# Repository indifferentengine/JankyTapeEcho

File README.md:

# Indifferent Engine Janky Tape Echo

An open-source, DIY tape echo effect pedal built from a cheap cassette player and 3D printed parts.

# Demo Video

This is kinda what this thing sounds like.

# License

This device is licensed under GNU GPL v3. This means you are free to take this device and make any changes you like and then share those changes freely, **so long as you make the source for your changes publicly available**. This benefits everyone - because if you make some improvement, we can all benefit from it.

However, you **cannot distribute compiled versions.** In this context (a hardware device with software components), this effectively means you

a)  **cannot sell any physically manufactured device of any kind - either as parts or assembled.** 

b) **cannot charge money for access to any source, CAD files or software components that you choose to distribute** that are based upon this project.
  
If you **break these simple rules** we will force you to be front row at one of our floor shows, where we can **full-throat scream right in your sad little face.**

Everything is copyright (c) 2023 Indifferent Engine Ltd. Everything. OK?
Indifferent Engine and the Indifferent Engine glitch logo are trademarks of Indifferent Engine Ltd.

# What You Get

* STL files for 3D printed parts
* Gerber files for PCBs
* Source code for Arduino
* Bill of Materials
* CAD files in Step format.
* Eagle schematic files.
* Eagle board blanks (boards of correct dimensions with Jacks in correct locations).
* Build instructions (via our website)

# What You Don't Get

* Full Eagle board files
* Any support from us what-so-ever.

# Build guide

To show you how to put one of these together, there is a [build guide](https://www.indifferentengine.com/tapeechobuildguide) on our website.

# PCB

We sell PCBs for this project on our [merch store](https://www.indifferentengine.com/shop).

# How can we support you?

Indifferent Engine is a band, so go check out our music here:
[spotify](https://open.spotify.com/artist/0dltTUV2N49r1UjUTsqe3h?si=cdwmojcwTOmE14S_XvX_6A)

If you're having a crack at building an echo, maybe buy some parts from us on our [merch store](https://www.indifferentengine.com/shop).. All money goes back into the band for funding musical endeavours and more weird, open source pedal designs.

You can also follow us in the usual places:
[instagram](https://www.instagram.com/indifferentengine)
[facebook](https://www.facebook.com/indifferentengine)
[tiktok](https://www.tiktok.com/@indifferentengine)
[youtube](https://www.youtube.com/@indifferentengine)

And **buy a T-Shirt while you're at it**, you bunch of scallywags.

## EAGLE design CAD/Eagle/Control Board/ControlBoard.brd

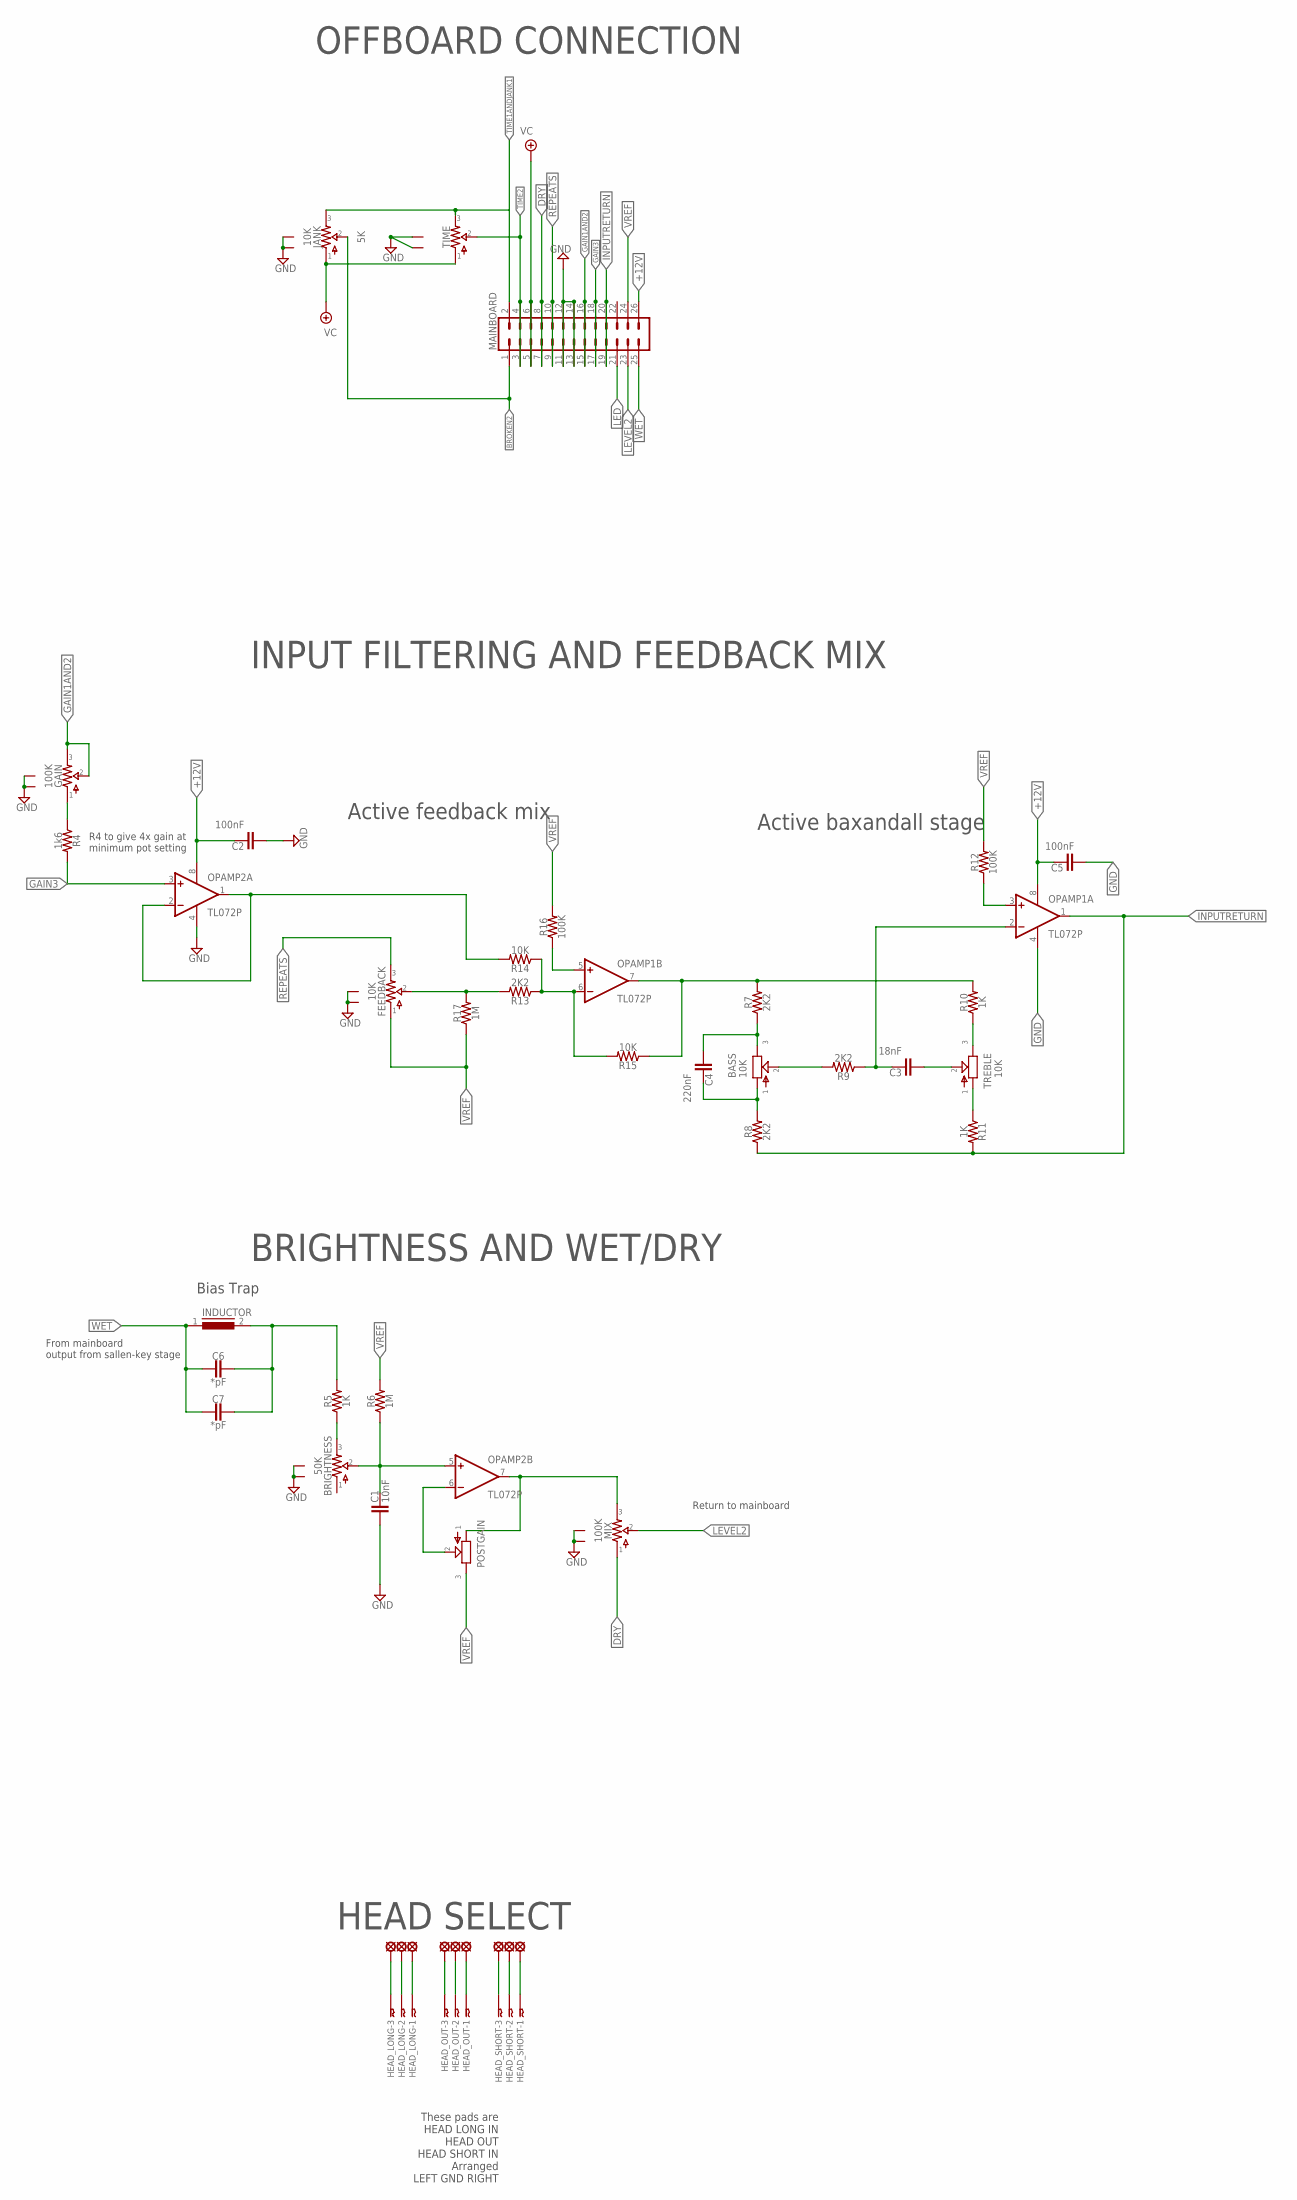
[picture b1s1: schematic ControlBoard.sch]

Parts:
BASS: 10K; B375P
BRIGHTNESS: 50K; 9MM_METAL_SHAFT
C1: 10nF; .33UF+
C2, C5: 100nF; 5MM
C3: 18nF; .33UF+
C4: 220nF; .33UF+
C6, C7: *pF; .33UF+
FEEDBACK: 10K; 9MM_METAL_SHAFT
GAIN: 100K; 9MM_METAL_SHAFT
HEAD_LONG: 03-JST-B3B-XH-A; B3B-XH
HEAD_OUT: 03-JST-B3B-XH-A; B3B-XH
HEAD_SHORT: 03-JST-B3B-XH-A; B3B-XH
HIN_1, HIN_2, HIN_3, HIN_4, HIN_5, HIN_6: SE14
HOUT_1, HOUT_2, HOUT_3: SE14
INDUCTOR: 82114R
JANK: 10K; 9MM_METAL_SHAFT
MAINBOARD: CONN_13X22X13; 2X13
MIX: 100K; 9MM_METAL_SHAFT
OPAMP1, OPAMP2: TL072P; DIL08
POSTGAIN: POT-EU375; B375P
R4: 1k6; 7.5MM.2
R5, R10, R11: 1K; 7.5MM.2
R6, R17: 1M; 7.5MM.2
R7, R8, R9, R13: 2K2; 7.5MM.2
R12, R16: 100K; 7.5MM.2
R14, R15: 10K; 7.5MM.2
TIME: 5K; 9MM_METAL_SHAFT
TREBLE: 10K; B375P

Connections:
+12V: C2.1, C5.1, MAINBOARD.26, OPAMP1.8 (V+), OPAMP2.8 (V+)
BIAS: C6.1, C7.1, INDUCTOR.2, R5.2
BRIGHTNESS2: OPAMP2.1 (OUT), OPAMP2.2 (-IN), R14.2
BROKEN2: JANK.P$2 (2), MAINBOARD.1
DRY: MAINBOARD.7, MAINBOARD.8, MIX.P$1 (1)
GAIN1AND2: GAIN.P$2 (2), GAIN.P$3 (3), MAINBOARD.15, MAINBOARD.16
GAIN3: MAINBOARD.17, MAINBOARD.18, OPAMP2.3 (+IN), R4.2
GND: BRIGHTNESS.P$4 (CHAS$1), BRIGHTNESS.P$5 (CHAS$2), C1.2, C2.2, C5.2, FEEDBACK.P$4 (CHAS$1), FEEDBACK.P$5 (CHAS$2), GAIN.P$4 (CHAS$1), GAIN.P$5 (CHAS$2), JANK.P$4 (CHAS$1), JANK.P$5 (CHAS$2), MAINBOARD.11, MAINBOARD.12, MAINBOARD.13, MAINBOARD.14, MIX.P$4 (CHAS$1), MIX.P$5 (CHAS$2), OPAMP1.4 (V-), OPAMP2.4 (V-), TIME.P$4 (CHAS$1), TIME.P$5 (CHAS$2)
INPUTRETURN: MAINBOARD.19, MAINBOARD.20, OPAMP1.1 (OUT), R8.1, R11.2
LED: MAINBOARD.21
LEVEL2: MAINBOARD.23, MIX.P$2 (2)
unnamed: BRIGHTNESS.P$2 (2), C1.1, OPAMP2.5 (+IN), R6.1
unnamed: HEAD_LONG.P$3, HIN_4.MP
unnamed: BASS.2, R9.2
unnamed: R10.1, TREBLE.3
unnamed: C3.2, TREBLE.2
unnamed: HEAD_LONG.P$2, HIN_5.MP
unnamed: HEAD_LONG.P$1, HIN_6.MP
unnamed: HEAD_OUT.P$3, HOUT_1.MP
unnamed: BRIGHTNESS.P$3 (3), R5.1
unnamed: HEAD_OUT.P$2, HOUT_2.MP
unnamed: HEAD_OUT.P$1, HOUT_3.MP
unnamed: OPAMP2.6 (-IN), POSTGAIN.2
unnamed: MIX.P$3 (3), OPAMP2.7 (OUT), POSTGAIN.1
unnamed: HEAD_SHORT.P$3, HIN_1.MP
unnamed: BASS.3, C4.2, R7.1
unnamed: BASS.1, C4.1, R8.2
unnamed: R11.1, TREBLE.1
unnamed: FEEDBACK.P$2 (2), R13.2, R17.2
unnamed: C3.1, OPAMP1.2 (-IN), R9.1
unnamed: OPAMP1.3 (+IN), R12.1
unnamed: OPAMP1.6 (-IN), R13.1, R14.1, R15.2
unnamed: OPAMP1.5 (+IN), R16.1
unnamed: HEAD_SHORT.P$2, HIN_2.MP
unnamed: HEAD_SHORT.P$1, HIN_3.MP
unnamed: GAIN.P$1 (1), R4.1
REPEATS: FEEDBACK.P$3 (3), MAINBOARD.9, MAINBOARD.10
TIME1ANDJANK1: JANK.P$3 (3), MAINBOARD.2, TIME.P$3 (3)
TIME2: MAINBOARD.3, MAINBOARD.4, TIME.P$2 (2)
TOBAXANDALL: OPAMP1.7 (OUT), R7.2, R10.2, R15.1
VC: JANK.P$1 (1), MAINBOARD.5, MAINBOARD.6, TIME.P$1 (1)
VREF: FEEDBACK.P$1 (1), MAINBOARD.24, POSTGAIN.3, R6.2, R12.2, R16.2, R17.1
WET: C6.2, C7.2, INDUCTOR.1, MAINBOARD.25

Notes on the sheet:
OFFBOARD CONNECTION
These pads are HEAD LONG IN HEAD OUT HEAD SHORT IN Arranged LEFT GND RIGHT
INPUT FILTERING AND FEEDBACK MIX
BRIGHTNESS AND WET/DRY
HEAD SELECT
R4 to give 4x gain at minimum pot setting
Active baxandall stage
Active feedback mix
Return to mainboard
From mainboard output from sallen-key stage
Bias Trap

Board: 2 copper layers, 46 parts (0 on the bottom side), 42 nets, no tracks yet.

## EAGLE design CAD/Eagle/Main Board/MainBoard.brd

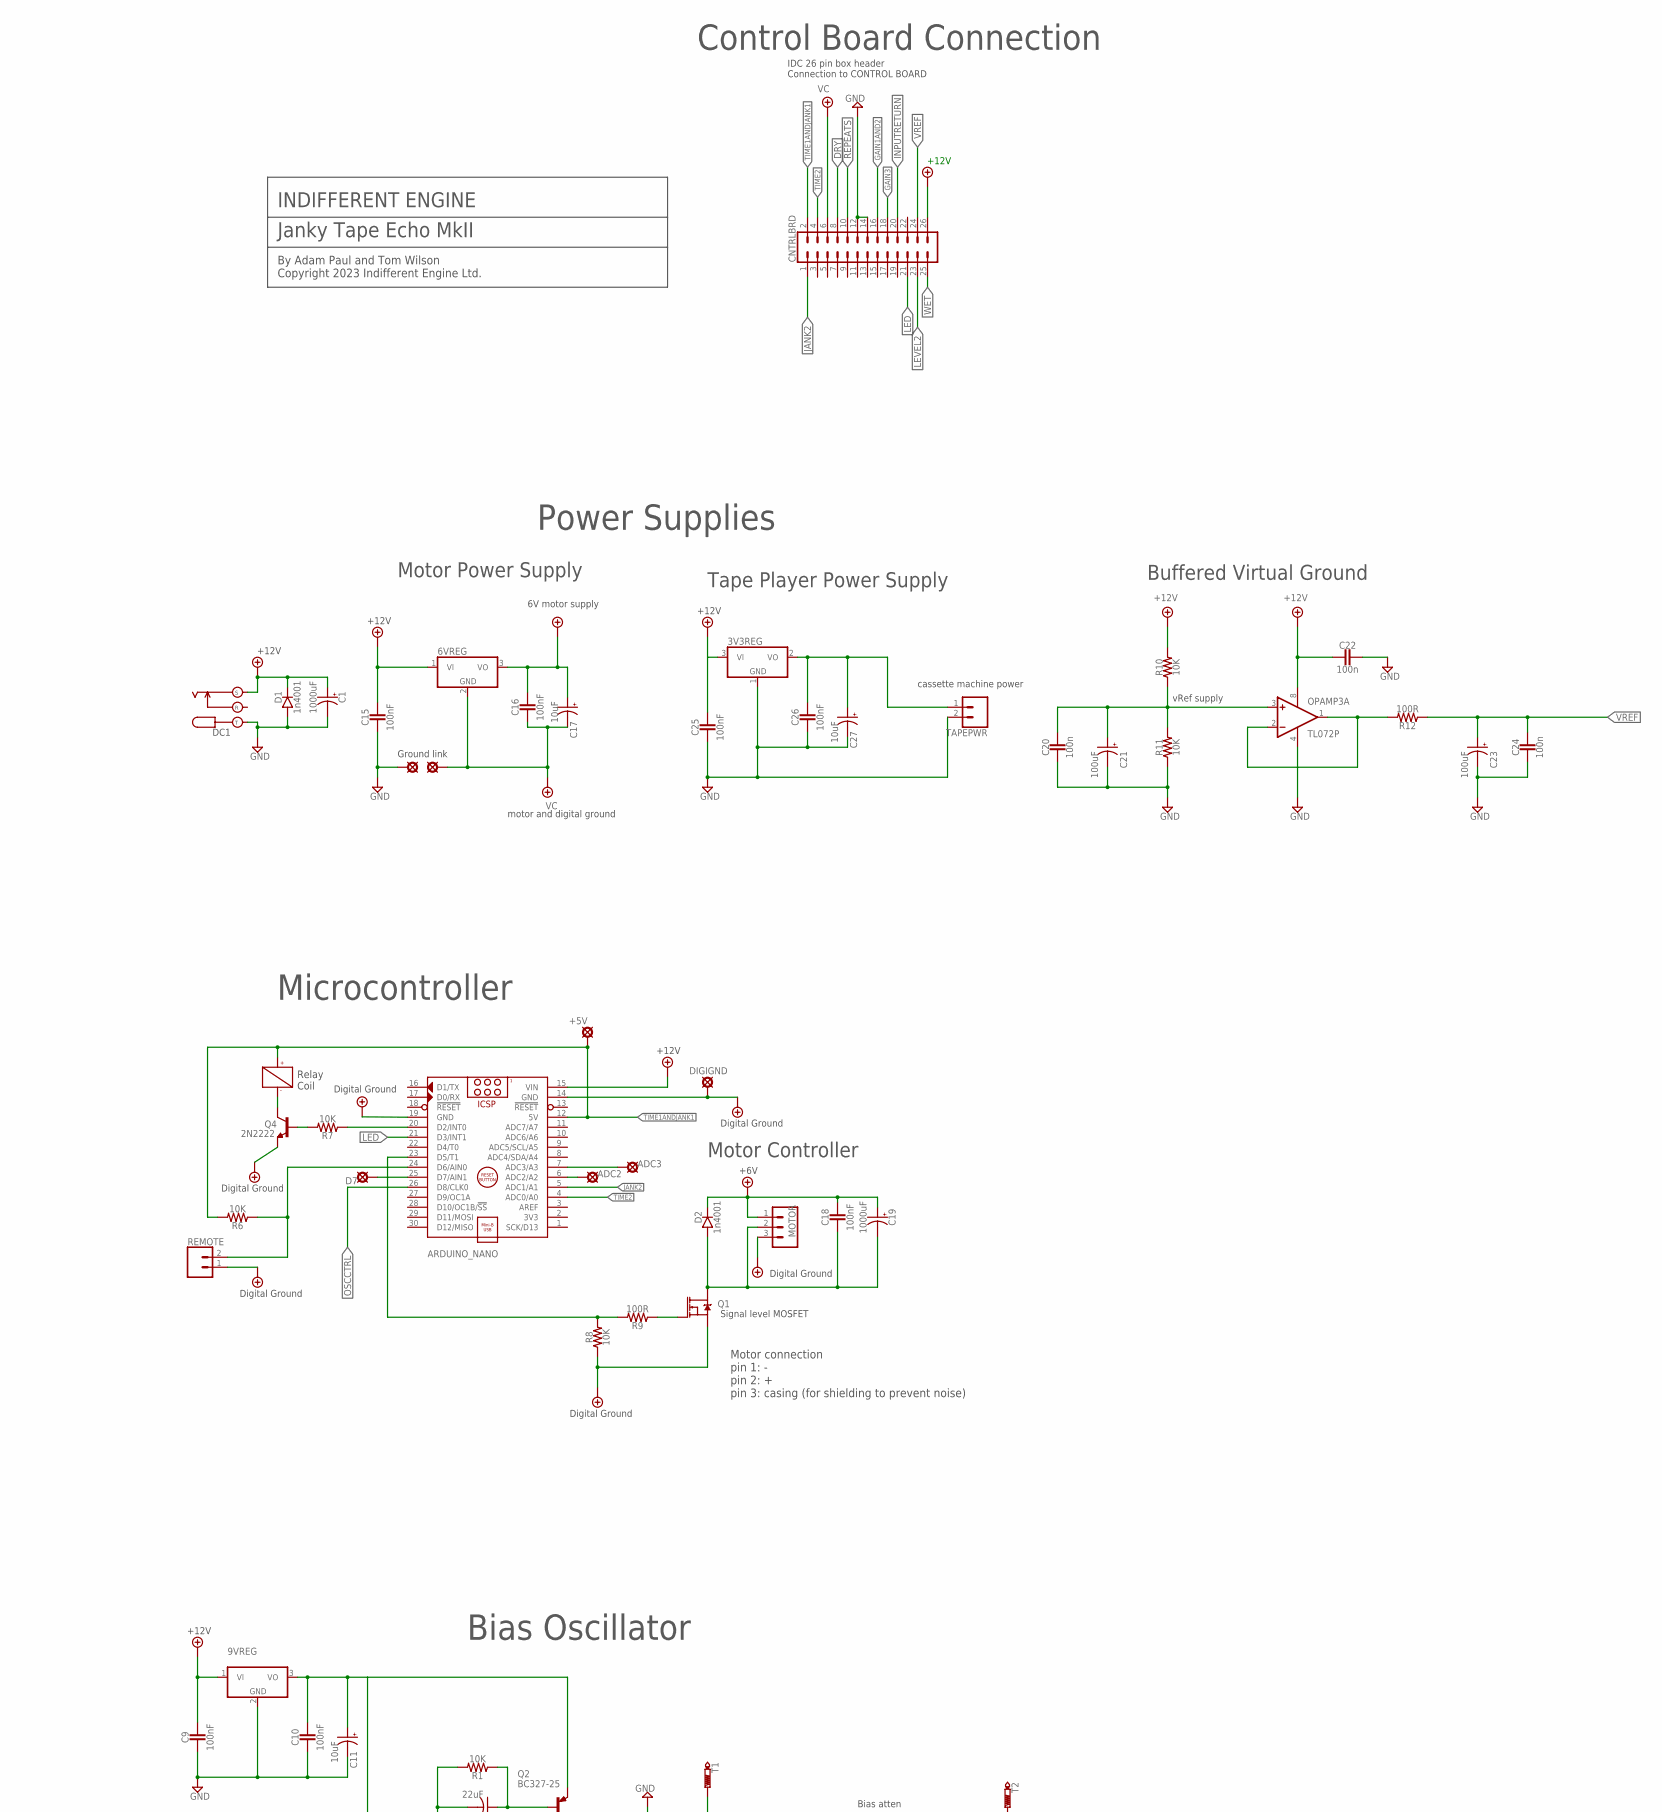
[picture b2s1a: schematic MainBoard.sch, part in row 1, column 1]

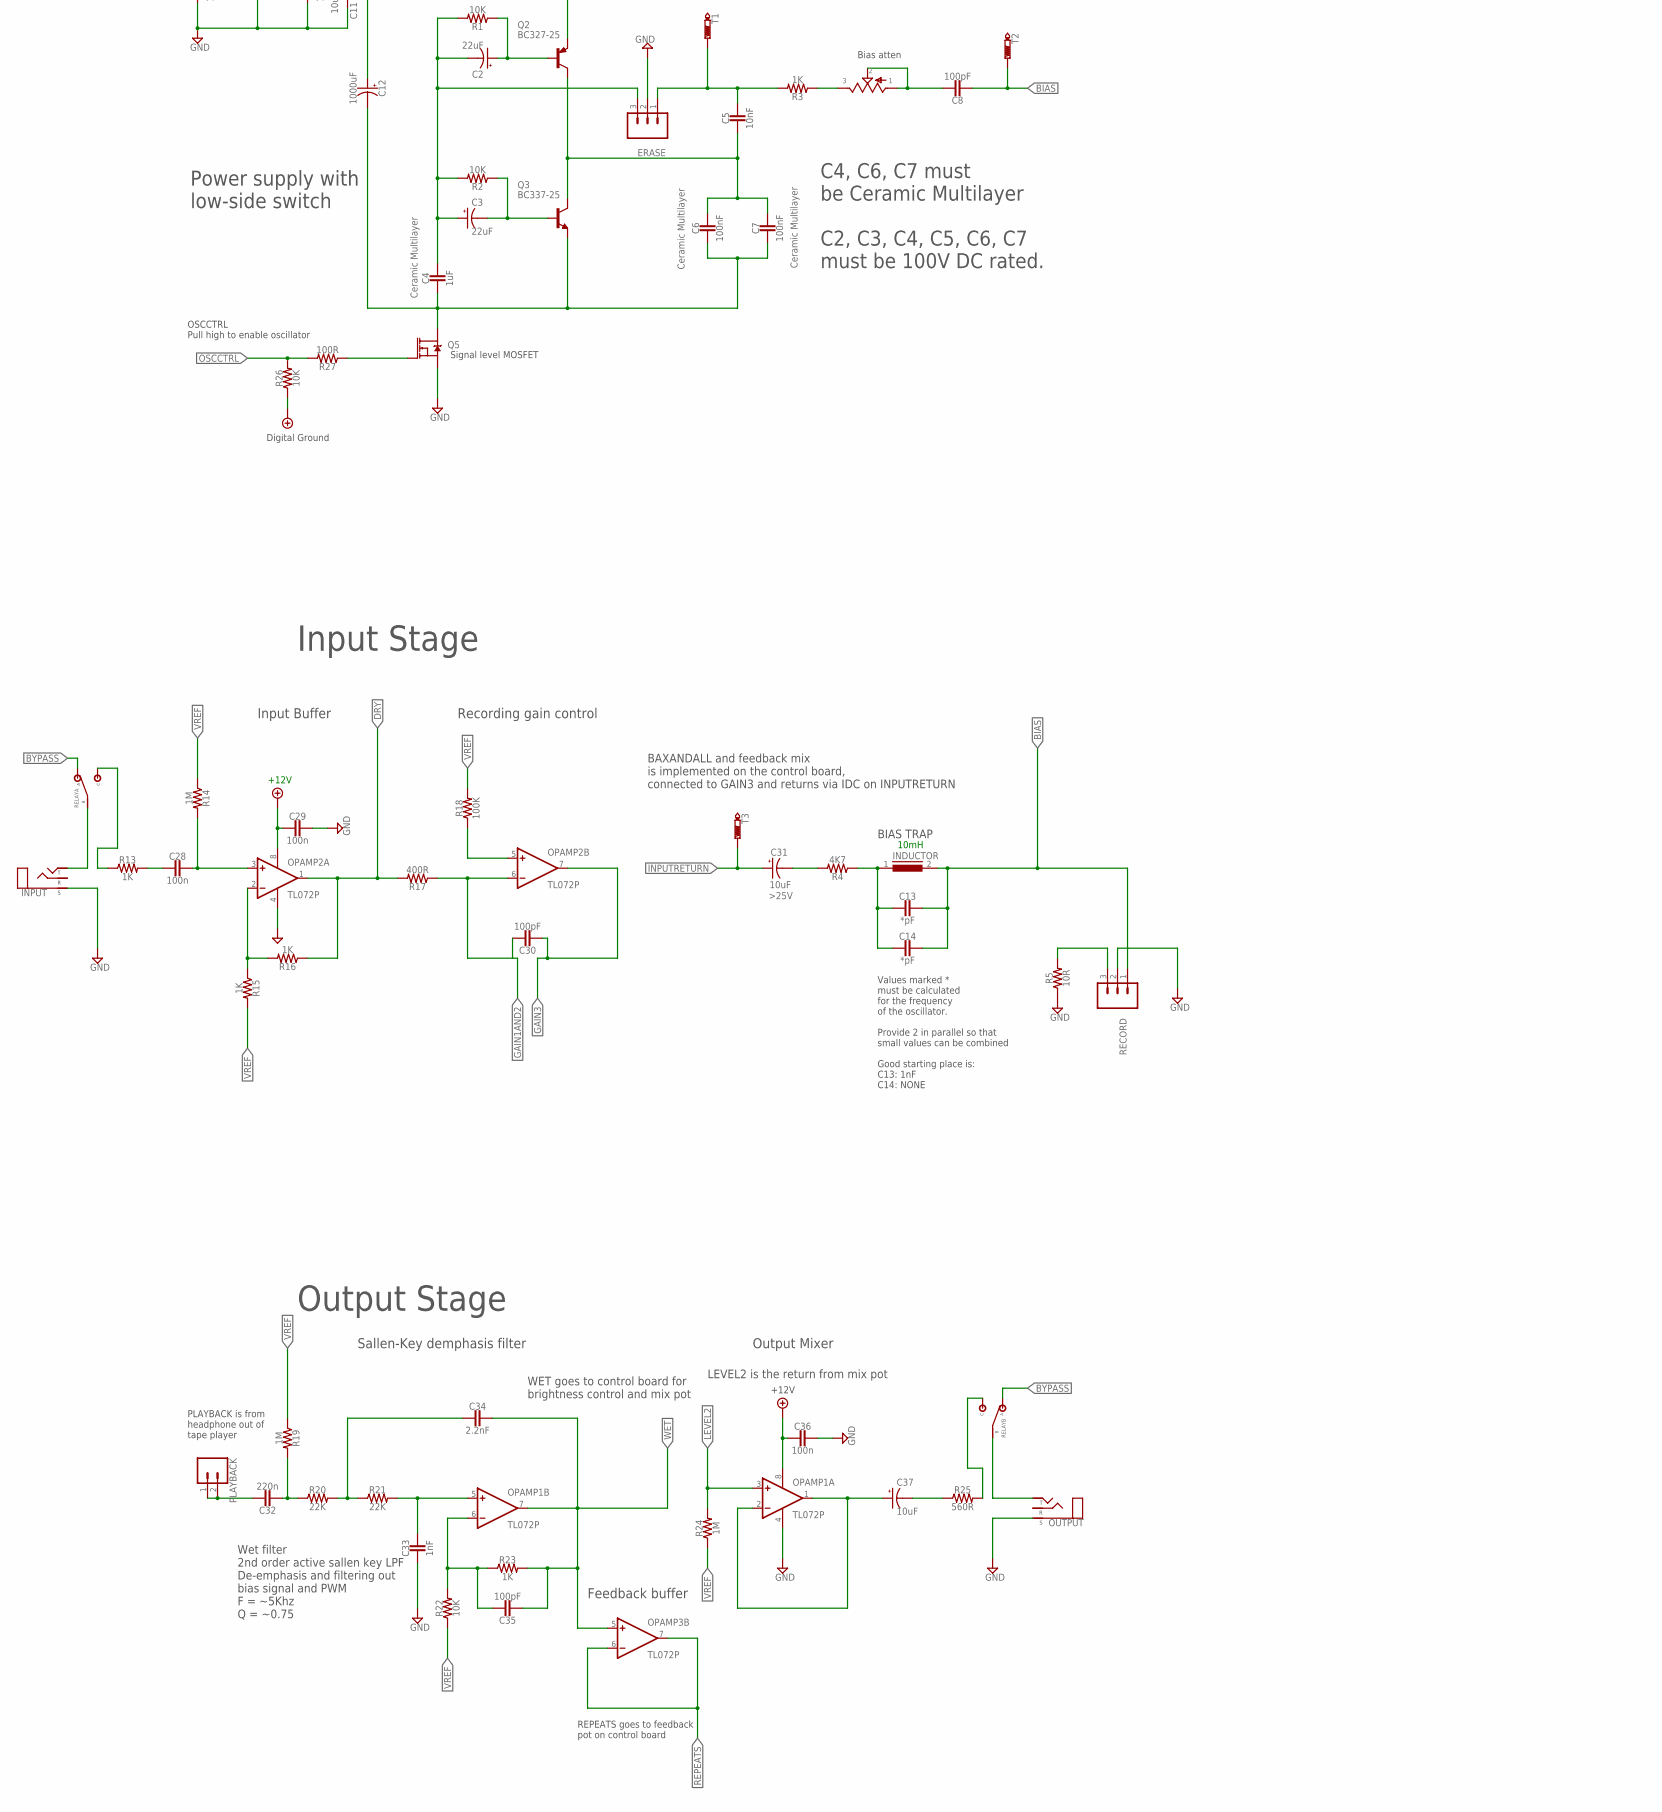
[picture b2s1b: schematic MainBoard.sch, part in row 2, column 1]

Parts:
3V3REG: 78TO220H_2_SMALL; TO220H_SMALL
6VREG, 9VREG: 78TO220H_SMALL; TO220H_SMALL
+5V: PADL; LONG
ADC2, ADC3: PADL; LONG
ANALOG_GND: PADL; LONG
ARDUINO_NANO: ARDUINO_NANO
BIASLEVEL: POTTRIM3/8; B375P
C1, C12, C19: 1000uF; 080_5MM
C2, C3: 22uF; 050_2.5MM.1
C4: 1uF; 5MM
C5: 10nF; 5MM
C6, C7, C9, C10, C15, C16, C25, C26: 100nF; 5MM
C8, C30, C35: 100pF; .33UF+
C11, C17, C27, C37: 10uF; 050_2.5MM.1
C13, C14: *pF; .33UF+
C18: 100nF; .33UF+
C20, C22, C24, C29, C36: 100n; 5MM
C21, C23: 100uF; 050_2.5MM.1
C28: 100n; .33UF+
C31: 10uF; 050_2.5MM.1; VOLTAGE >25V
C32: 220n; .33UF+
C33: 1nF; .33UF+
C34: 2.2nF; .33UF+
CNTRLBRD: CONN_13X22X13; 2X13
D1, D2: 1n4001; DO41-3
D7: PADL; LONG
DC1: DC_KOBICONN
DIGIGND: PADL; LONG
DIGI_GROUND: PADL; LONG
ERASE: 455-1750-1-ND; 1X03
INDUCTOR: 82114R
INPUT: STEREO; STEREO_PCB
MOTOR: 455-1750-1-ND; 1X03
OPAMP1, OPAMP2, OPAMP3: TL072P; DIL08
OUTPUT: STEREO; STEREO_PCB
PLAYBACK: CONN_02; 1X02
Q1, Q5: 60V/32A/35mΩ; TO220V
Q2: BC327-25; TO92-EBC
Q3: BC337-25TO92; TO92-EBC
Q4: 2N2222; TO92-
R1, R2, R6, R7, R8, R10, R11, R22, R26: 10K; 7.5MM.2
R3, R13, R15, R16, R23: 1K; 7.5MM.2
R4: 4K7; 7.5MM.2
R5: 10R; 7.5MM.2
R9, R12, R27: 100R; 7.5MM.2
R14, R19, R24: 1M; 7.5MM.2
R17: 400R; 7.5MM.2
R18: 100K; 7.5MM.2
R20, R21: 22K; 7.5MM.2
R25: 560R; 7.5MM.2
RECORD: 455-1750-1-ND; 1X03
RELAY: IM02TSIM02TS; 8-PIN
REMOTE: CONN_02; 1X02
T1, T2, T3: PTR1B2,54; B2,54
TAPEPWR: CONN_02; 1X02

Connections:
+12V: 3V3REG.3 (VI), 6VREG.1 (VI), 9VREG.1 (VI), ARDUINO_NANO.15 (VIN), C1.+, C9.1, C15.1, C22.2, C25.1, C29.2, C36.2, CNTRLBRD.26, D1.C, DC1.S, OPAMP1.8 (V+), OPAMP2.8 (V+), OPAMP3.8 (V+), R10.2
BIAS: C8.2, C13.1, C14.1, INDUCTOR.2, RECORD.1, T2.TP
BYPASS: RELAY.3 (A), RELAY.10 (A)
DRY: CNTRLBRD.8, OPAMP2.1 (OUT), R16.1, R17.2
GAIN1AND2: C30.1, CNTRLBRD.16, OPAMP2.6 (-IN), R17.1
GAIN3: C30.2, CNTRLBRD.18, OPAMP2.7 (OUT)
GND: 3V3REG.1 (GND), 9VREG.2 (GND), ANALOG_GND.1, C1.-, C9.2, C10.2, C11.-, C15.2, C20.2, C21.-, C22.1, C23.-, C24.2, C25.2, C26.2, C27.-, C29.1, C33.2, C36.1, CNTRLBRD.12, CNTRLBRD.14, D1.A, DC1.T, ERASE.2, INPUT.P$1 (S), OPAMP1.4 (V-), OPAMP2.4 (V-), OPAMP3.4 (V-), OUTPUT.P$1 (S), Q5.3 (S), R5.1, R11.1, RECORD.2, TAPEPWR.2
INPUTRETURN: C31.+, CNTRLBRD.20, T3.TP
JANK2: ARDUINO_NANO.5 (ADC1/A1), CNTRLBRD.1
LED: ARDUINO_NANO.21 (D3/INT1), CNTRLBRD.21
LEVEL2: CNTRLBRD.23, OPAMP1.3 (+IN), R24.2
unnamed: INPUT.P$3 (T), RELAY.4 (B)
unnamed: ARDUINO_NANO.23 (D5/T1), R8.2, R9.2
unnamed: C18.2, C19.-, D2.A, MOTOR.2, Q1.2 (D)
unnamed: Q1.1 (G), R9.1
unnamed: C28.2, R13.2
unnamed: OPAMP2.5 (+IN), R18.1
unnamed: OPAMP2.2 (-IN), R15.1, R16.2
unnamed: C13.2, C14.2, INDUCTOR.1, R4.1
unnamed: Q5.1 (G), R27.1
unnamed: R5.2, RECORD.3
unnamed: R13.1, RELAY.5 (C)
unnamed: C33.1, OPAMP1.5 (+IN), R21.2
unnamed: C32.2, R19.2, R20.1
unnamed: C35.1, OPAMP1.6 (-IN), R22.2, R23.1
unnamed: C20.1, C21.+, OPAMP3.3 (+IN), R10.1, R11.2
unnamed: C34.2, R20.2, R21.1
unnamed: C28.1, OPAMP2.3 (+IN), R14.2
unnamed: C37.+, OPAMP1.1 (OUT), OPAMP1.2 (-IN)
unnamed: C37.-, R25.1
unnamed: R25.2, RELAY.8 (C)
unnamed: C2.+, Q2.B, R1.1
unnamed: C3.-, Q3.B, R2.1
unnamed: C2.-, C3.+, C4.1, ERASE.3, R1.2, R2.2
unnamed: C5.2, C6.1, C7.1, Q2.C, Q3.C
unnamed: C5.1, ERASE.1, R3.2, T1.TP
unnamed: BIASLEVEL.3, R3.1
unnamed: OUTPUT.P$3 (T), RELAY.9 (B)
unnamed: Q4.2 (B), R7.2
unnamed: BIASLEVEL.1, BIASLEVEL.2, C8.1
unnamed: C31.-, R4.2
unnamed: ARDUINO_NANO.20 (D2/INT0), R7.1
unnamed: Q4.1 (C), RELAY.1 (-)
unnamed: ARDUINO_NANO.24 (D6/AIN0), R6.1, REMOTE.2
unnamed: OPAMP3.1 (OUT), OPAMP3.2 (-IN), R12.2
unnamed: 9VREG.3 (VO), C10.1, C11.+, C12.+, Q2.E
unnamed: 3V3REG.2 (VO), C26.1, C27.+, TAPEPWR.1
unnamed: C4.2, C6.2, C7.2, C12.-, Q3.E, Q5.2 (D)
unnamed: ADC2.1, ARDUINO_NANO.6 (ADC2/A2)
unnamed: ADC3.1, ARDUINO_NANO.7 (ADC3/A3)
unnamed: ARDUINO_NANO.25 (D7/AIN1), D7.1
OSCCTRL: ARDUINO_NANO.26 (D8/CLK0), R26.2, R27.2
PLAYBACK: C32.1, PLAYBACK.1, PLAYBACK.2
REPEATS: CNTRLBRD.10, OPAMP3.6 (-IN), OPAMP3.7 (OUT)
TIME1ANDJANK1: +5V.1, ARDUINO_NANO.12 (5V), CNTRLBRD.2, R6.2, RELAY.12 (+)
TIME2: ARDUINO_NANO.4 (ADC0/A0), CNTRLBRD.4
VC: 6VREG.2 (GND), ARDUINO_NANO.14 (GND), ARDUINO_NANO.19 (GND), C16.2, C17.-, CNTRLBRD.6, DIGIGND.1, DIGI_GROUND.1, MOTOR.3, Q1.3 (S), Q4.3 (E), R8.1, R26.1, REMOTE.1
VD: 6VREG.3 (VO), C16.1, C17.+, C18.1, C19.+, D2.C, MOTOR.1
VREF: C23.+, C24.1, CNTRLBRD.24, R12.1, R14.1, R15.2, R18.2, R19.1, R22.1, R24.1
WET: C34.1, C35.2, CNTRLBRD.25, OPAMP1.7 (OUT), OPAMP3.5 (+IN), R23.2

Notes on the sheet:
6V motor supply
Motor Power Supply
Motor Controller
Input Buffer
vRef supply
BIAS TRAP
Wet filter 2nd order active sallen key LPF De-emphasis and filtering out bias signal and PWM F = ~5Khz Q = ~0.75
Output Mixer
BC337-25
Ceramic Multilayer
IDC 26 pin box header Connection to CONTROL BOARD
10mH
Bias atten
+12V
Relay Coil
Digital Ground
+6V
Signal level MOSFET
Control Board Connection
INDIFFERENT ENGINE
Janky Tape Echo MkII
By Adam Paul and Tom Wilson Copyright 2023 Indifferent Engine Ltd.
motor and digital ground
cassette machine power
Values marked * must be calculated for the frequency of the oscillator. Provide 2 in parallel so that small values can be combined Good starting place is: C13: 1nF C14: NONE
REPEATS goes to feedback pot on control board
Feedback buffer
PLAYBACK is from headphone out of tape player
Recording gain control
BAXANDALL and feedback mix is implemented on the control board, connected to GAIN3 and returns via IDC on INPUTRETURN
Power Supplies
Buffered Virtual Ground
Microcontroller
Bias Oscillator
Input Stage
Output Stage
Motor connection pin 1: - pin 2: + pin 3: casing (for shielding to prevent noise)
OSCCTRL Pull high to enable oscillator
Tape Player Power Supply
Power supply with low-side switch

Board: 2 copper layers, 101 parts (0 on the bottom side), 60 nets, no tracks yet.

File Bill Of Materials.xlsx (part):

This page contains the electronic parts in order of usage in the build instruct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
The Jacks
Part | Value | Description | Notes
INPUT | Audio Jack | PCB mount 3/4" audio jack
OUTPUT | Audio Jack | PCB mount 3/4" audio jack
DC1 | DC Jack | Boss-style 2.1mm DC Jack
The Ground Link
GND LINK | 0R | Zero Ohm Link | This is just a 0 Ohm link between the digital ground and analog ground. This is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
The JST XH Headers
ERASE | 2-way JST XH Header | 2-way JST XH Male Terminal. 2.54mm lead pitch.
PLAYBACK | 2-way JST XH Header | 2-way JST XH Male Terminal. 2.54mm lead pitch.
RECORD | 2-way JST XH Header | 2-way JST XH Male Terminal. 2.54mm lead pitch.
REMOTE | 2-way JST XH Header | 2-way JST XH Male Terminal. 2.54mm lead pitch.
TAPEPWR | 2-way JST XH Header | 2-way JST XH Male Terminal. 2.54mm lead pitch.
MOTOR | 3-way JST XH Header | 3-way JST XH Male Terminal. 2.54mm lead pitch. | We use a 3 way header because we use a spare pin to ground the motor casing. Th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
The IDC Box Header
CNTRLBRD | IDC Box Header | 26-way IDC box header for connection to control board | Must be a 26-way, 2 row IDC box header.
12V Main Supply
D1 | 1n4001 | Polarity protection diode
C1 | 1000uF | Electrolytic capacitor, 16V, 8mm diameter
9V Bias Oscillator Supply
R26 | 10K | 1/4W Metal Film Resistor, 7.5mm diameter
R27 | 100R | 1/4W Metal Film Resistor, 7.5mm diameter
C9 | 100nF | Ceramic capacitor, 16V, 5mm diameter
C10 | 100nF | Ceramic capacitor, 16V, 5mm diameter
C11 | 10uF | Electrolytic capacitor, 16V, 5mm diameter
C12 | 1000uF | Electrolytic capacitor, 16V, 8mm diameter
9VREG | 7809.0 | Positive VOLTAGE REGULATOR, 9V Output | Ensure correct pinout: INPUT, GND, OUTPUT
Q5 | RFP12N10L | N-channel, logic level MOSFET | For oscillator disable control
6V Motor Supply
6VREG | 7806.0 | Positive VOLTAGE REGULATOR, 6V Output | Ensure correct pinout: INPUT, GND, OUTPUT
C15 | 100nF | Ceramic capacitor, 16V, 5mm diameter
C16 | 100nF | Ceramic capacitor, 16V, 5mm diameter
C17 | 10uF | Electrolytic capacitor, 16V, 5mm diameter
3V3 Tape Player Supply
3V3REG | LD1086V33 | Positive VOLTAGE REGULATOR, 3.3V Output | Ensure correct pinout: GND, OUTPUT, INPUT This is different to the other 2 regu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
C25 | 100nF | Ceramic capacitor, 16V, 5mm diameter
C26 | 100nF | Ceramic capacitor, 16V, 5mm diameter
C27 | 10uF | Electrolytic capacitor, 16V, 5mm diameter
Buffered Virtual Ground
R10 | 10K | 1/4W Metal Film Resistor, 7.5mm diameter
R11 | 10K | 1/4W Metal Film Resistor, 7.5mm diameter
R12 | 100R | 1/4W Metal Film Resistor, 7.5mm diameter
OPAMP3 | TL072 | TL072 Dual Op Amp (or equivalent)
C20 | 100n | Ceramic capacitor, 16V, 5mm diameter
C21 | 100uF | Electrolytic capacitor, 16V, 5mm diameter
C22 | 100n | Ceramic capacitor, 16V, 5mm diameter
C23 | 100uF | Electrolytic capacitor, 16V, 5mm diameter
C24 | 100n | Ceramic capacitor, 16V, 5mm diameter
Arduino Nano
ARDUINO_NANO | Arduino Nano | Arduino Nano V3.0 Module
True Bypass Switching
R6 | 10K | 1/4W Metal Film Resistor, 7.5mm diameter
R7 | 10K | 1/4W Metal Film Resistor, 7.5mm diameter
Q4 | 2N2222 | NPN Transistor | For relay bypass switching
RELAY | 5-1462039-9 | Non-Latching, DPDT Signal Relay, 5V | https://uk.farnell.com/te-connectivity/im03pns/relay-signal-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
The Motor Controller
R8 | 10K | 1/4W Metal Film Resistor, 7.5mm diameter
R9 | 100R | 1/4W Metal Film Resistor, 7.5mm diameter
D2 | 1n4001 | Back propagation protection diode
Q1 | RFP12N10L | N-channel, logic level MOSFET | High current MOSFET for motor control. Must be logic level to interface with Ar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
C18 | 100nF | Ceramic capacitor, 16V, 5mm diameter
C19 | 1000uF | Electrolytic capacitor, 16V, 8mm diameter
Mainboard Input Stage
R4 | 4K7 | 1/4W Metal Film Resistor, 7.5mm diameter
R5 | 0R | 1/4W Metal Film Resistor, 7.5mm diameter | This is included as a way to adjust coil resistance for tuning purposes. If in 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
R13 | 1K | 1/4W Metal Film Resistor, 7.5mm diameter
R14 | 1M | 1/4W Metal Film Resistor, 7.5mm diameter
R15 | 1K | 1/4W Metal Film Resistor, 7.5mm diameter
R16 | 1K | 1/4W Metal Film Resistor, 7.5mm diameter
R17 | 400R | 1/4W Metal Film Resistor, 7.5mm diameter
R18 | 100K | 1/4W Metal Film Resistor, 7.5mm diameter
OPAMP2 | TL072 | TL072 Dual Op Amp (or equivalent)
C13 | *pF | Film capacitor, 100V, 5mm diameter | For tuning bias trap notch filter. A good starting place is C13 as 1nF and C14 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
C14 | *pF | Film capacitor, 100V, 5mm diameter | Optional. Extra capacitor space for combining values with C13 (to make non-stan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
C28 | 100n | Film capacitor, 16V, 5mm diameter
C29 | 100n | Ceramic capacitor, 16V, 5mm diameter
C30 | 100pF | Film capacitor, 16V, 5mm diameter
C31 | 10uF | Electrolytic capacitor, 100V, 5mm diameter | Must be 100V rated
INDUCTOR | 10mH | Radial Inductor | For bias trap. If different value used, capacitors C13 and C14 in the tank circ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
Mainboard Output Stage
R19 | 1M | 1/4W Metal Film Resistor, 7.5mm diameter
R20 | 22K | 1/4W Metal Film Resistor, 7.5mm diameter
R21 | 22K | 1/4W Metal Film Resistor, 7.5mm diameter
R22 | 10K | 1/4W Metal Film Resistor, 7.5mm diameter
R23 | 1K | 1/4W Metal Film Resistor, 7.5mm diameter
R24 | 1M | 1/4W Metal Film Resistor, 7.5mm diameter
R25 | 560R | 1/4W Metal Film Resistor, 7.5mm diameter
OPAMP1 | TL072 | TL072 Dual Op Amp (or equivalent)
C32 | 220n | Film capacitor, 16V, 5mm diameter
C33 | 1nF | Film capacitor, 16V, 5mm diameter
C34 | 2.2nF | Film capacitor, 16V, 5mm diameter
C35 | 100pF | Film capacitor, 16V, 5mm diameter
C36 | 100n | Ceramic capacitor, 16V, 5mm diameter
C37 | 10uF | Electrolytic capacitor, 16V, 5mm diameter
Control Board IDC Header
MAINBOARD | IDC Box Header | 26-way IDC box header for connection to control board | Must be a 26-way, 2 row IDC box header.
Control Board JST XH Headers
HEAD_LONG | 3-way JST XH Header | 3-way JST XH Male Terminal. 2.54mm lead pitch.
HEAD_OUT | 3-way JST XH Header | 3-way JST XH Male Terminal. 2.54mm lead pitch.
HEAD_SHORT | 3-way JST XH Header | 3-way JST XH Male Terminal. 2.54mm lead pitch.
Control Board Bias Trap
INDUCTOR | 10mH | Radial Inductor | For bias trap. If different value used, capacitors C6 and C7 in the tank circui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
C6 | *pF | Film capacitor, 16V, 5mm diameter | For tuning bias trap notch filter. A good starting place is C13 as 1nF and C14 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
C7 | *pF | Film capacitor, 16V, 5mm diameter | Optional. Extra capacitor space for combining values with C13 (to make non-stan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
Control Board Input Filtering and Feedback Mix
R4 | 1K6 | 1/4W Metal Film Resistor, 7.5mm diameter
R7 | 2K2 | 1/4W Metal Film Resistor, 7.5mm diameter
R8 | 2K2 | 1/4W Metal Film Resistor, 7.5mm diameter
R9 | 2K2 | 1/4W Metal Film Resistor, 7.5mm diameter
R10 | 1K | 1/4W Metal Film Resistor, 7.5mm diameter
R11 | 1K | 1/4W Metal Film Resistor, 7.5mm diameter
R12 | 100K | 1/4W Metal Film Resistor, 7.5mm diameter
R13 | 2K2 | 1/4W Metal Film Resistor, 7.5mm diameter
R14 | 10K | 1/4W Metal Film Resistor, 7.5mm diameter
R15 | 10K | 1/4W Metal Film Resistor, 7.5mm diameter
R16 | 100K | 1/4W Metal Film Resistor, 7.5mm diameter
R17 | 1M | 1/4W Metal Film Resistor, 7.5mm diameter
OPAMP1 | TL072 | TL072 Op Amp (or equivalent)
OPAMP2 | TL072 | TL072 Op Amp (or equivalent)
BASS | 10K | Trimpot
TREBLE | 10K | Trimpot
C2 | 100nF | Ceramic capacitor, 16V, 5mm diameter
C3 | 18nF | Film capacitor, 16V, 5mm diameter
C4 | 220nF | Film capacitor, 16V, 5mm diameter
C5 | 100nF | Ceramic capacitor, 16V, 5mm diameter
Control Board Output Stage
R5 | 1K | 1/4W Metal Film Resistor, 7.5mm diameter
R6 | 1M | 1/4W Metal Film Resistor, 7.5mm diameter
POSTGAIN | 10K | Trimpot
C1 | 10nF | Film capacitor, 16V, 5mm diameter
Front Panel Potentiometers
TIME | 10K Linear | 9mm Alpha Potentiometer, Metal D-Shaft
BRIGHTNES | 50K Linear | 9mm Alpha Potentiometer, Metal D-Shaft
FEEDBACK | 10K Linear | 9mm Alpha Potentiometer, Metal D-Shaft
GAIN | 10K Linear | 9mm Alpha Potentiometer, Metal D-Shaft
MIX | 100K Linear | 9mm Alpha Potentiometer, Metal D-Shaft
JANK | 10K Linear | 9mm Alpha Potentiometer, Metal D-Shaft
Head Select Switch
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
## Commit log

2023-03-04 Janky Tape Echo v2.00 release
2023-03-04 Update README.txt
    Updated head adapter readme
2023-03-06 Update README.md
    Updated demo video link
2023-03-06 Update README.md
    Change of video link, again. :/
2023-06-20 -Increased thickness of lid front slightly to improve print reliability. -Added TC62 and 25PBK8 head adapters

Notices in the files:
parts and their libraries:
SparkFun-Connectors: Licensing: Creative Commons ShareAlike 4.0 International - https://creativecommons.org/licenses/by-sa/4.0
